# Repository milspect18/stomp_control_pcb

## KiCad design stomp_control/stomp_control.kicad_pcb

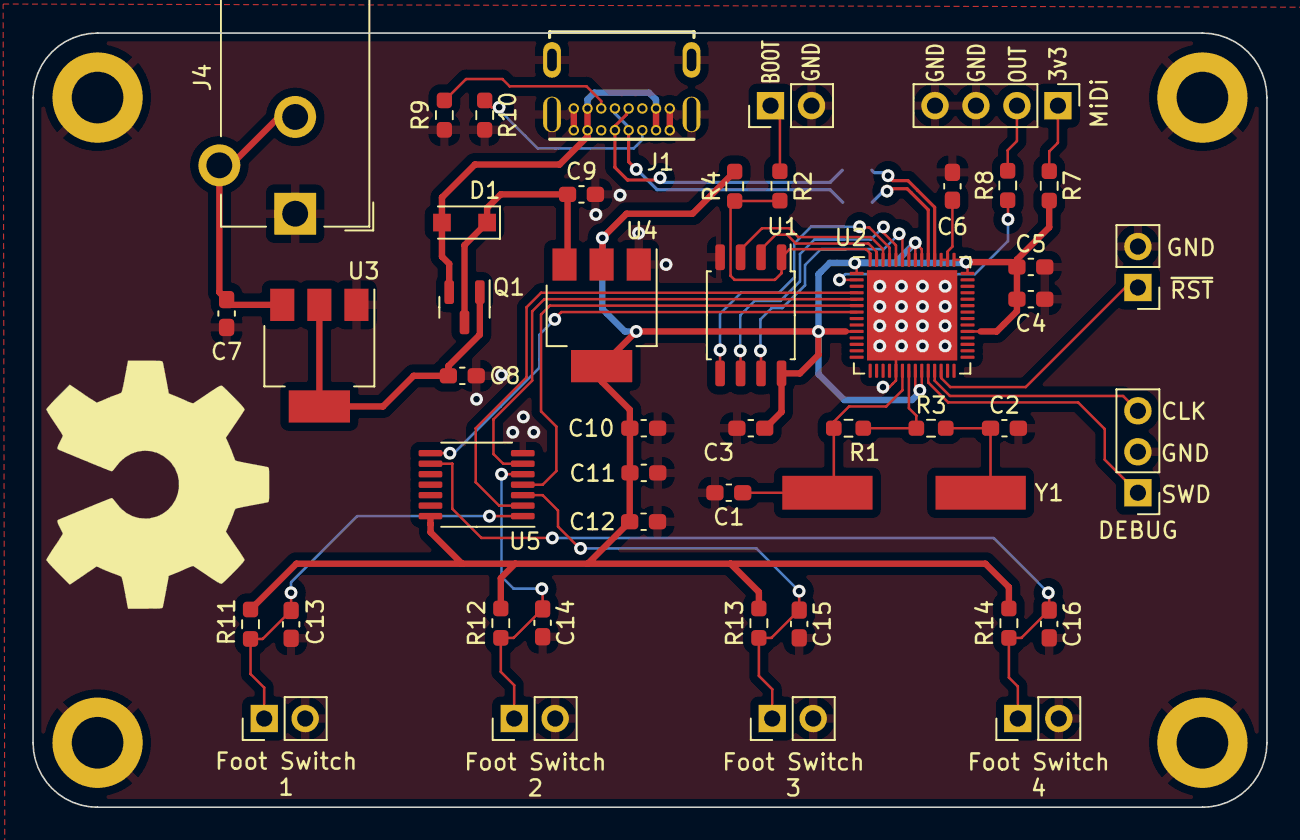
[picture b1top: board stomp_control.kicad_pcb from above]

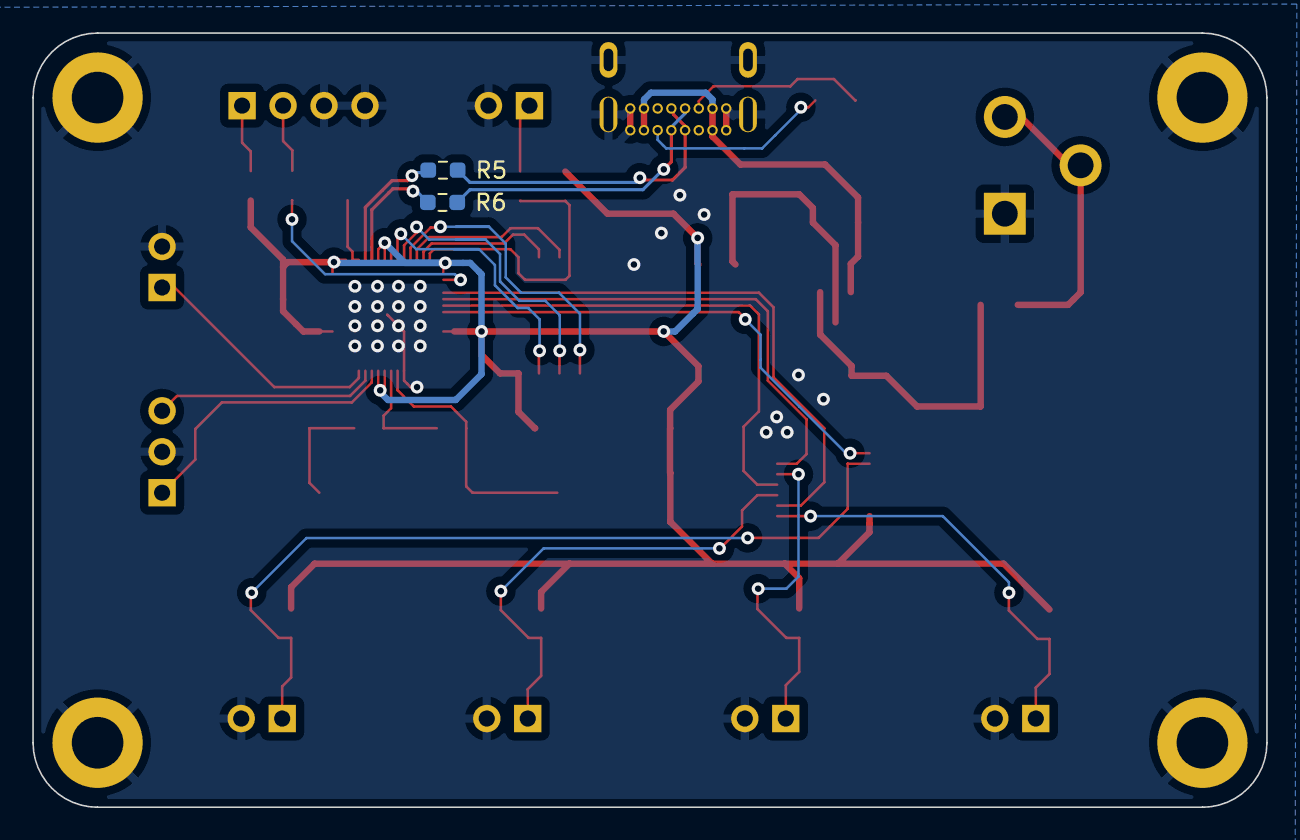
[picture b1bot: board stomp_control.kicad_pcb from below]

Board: 2 copper layers, 76.5 x 48.0 mm, 52 parts (2 on the bottom side), 37 nets.

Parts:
C1, C2: 15p; C_0603_1608Metric_Pad1.08x0.95mm_HandSolder
C3, C4, C13, C14, C15, C16: 100n; C_0603_1608Metric_Pad1.08x0.95mm_HandSolder
C5, C6: 2u2; C_0603_1608Metric_Pad1.08x0.95mm_HandSolder
C7, C8, C9, C10: 10uF; C_0603_1608Metric_Pad1.08x0.95mm_HandSolder
C11, C12: 10nF; C_0603_1608Metric_Pad1.08x0.95mm_HandSolder
D1: MBR1020VL; D_SOD-123F
DEBUG: SWD; PinHeader_1x03_P2.54mm_Vertical
H1, H2, H3, H4: MountingHole_Pad; MountingHole_3.2mm_M3_DIN965_Pad
J1: USB_C_Receptacle_USB2.0; GCT_USB4085-GF-A_REVA
J2: PROG_MODE; PinHeader_1x02_P2.54mm_Vertical
J3: RESET; PinHeader_1x02_P2.54mm_Vertical
J4: 9V center: Neg; BarrelJack_CUI_PJ-102AH_Horizontal
J5: Conn_01x04_Female; PinHeader_1x04_P2.54mm_Vertical
J6: FS_1; PinHeader_1x02_P2.54mm_Vertical
J7: FS_2; PinHeader_1x02_P2.54mm_Vertical
J8: FS_3; PinHeader_1x02_P2.54mm_Vertical
J9: FS_4; PinHeader_1x02_P2.54mm_Vertical
Q1: DMG2305UX; SOT-23
R1, R4: DNF; R_0603_1608Metric_Pad0.98x0.95mm_HandSolder
R2, R3: 1k; R_0603_1608Metric_Pad0.98x0.95mm_HandSolder
R5, R6: 27.4R; R_0603_1608Metric_Pad0.98x0.95mm_HandSolder
R7: 33R; R_0603_1608Metric_Pad0.98x0.95mm_HandSolder
R8: 10R; R_0603_1608Metric_Pad0.98x0.95mm_HandSolder
R9, R10: 5.1k; R_0603_1608Metric_Pad0.98x0.95mm_HandSolder
R11, R12, R13, R14: 220k; R_0603_1608Metric_Pad0.98x0.95mm_HandSolder
U1: W25Q128JVS; SOIC-8_5.23x5.23mm_P1.27mm
U2: RP2040; QFN-56-1EP_7x7mm_P0.4mm_EP5.6x5.6mm
U3: LM1117MP-5.0_NOPB; SOT-223
U4: LMS8117AMP-3.3_NOPB; SOT-223
U5: 74HC14; TSSOP-14_4.4x5mm_P0.65mm
Y1: 12MHz; ABLS-12.000MHZ-20-B-3-H-T

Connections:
/FootSwitches/3v3: C3.1, C4.1, C5.1, C10.1, C11.1, C12.1, R4.2, R7.2, R11.1, R12.1, R13.1, R14.1, U1.8 (VCC), U2.1 (IOVDD), U2.10 (IOVDD), U2.22 (IOVDD), U2.23 (DVDD), U2.33 (IOVDD), U2.42 (IOVDD), U2.43 (ADC_AVDD), U2.48 (USB_VDD), U2.49 (IOVDD), U2.50 (DVDD), U4.2 (VO), U4.4 (VO), U5.14 (VCC)
/FootSwitches/foot_switch_four: U2.7 (GPIO5), U5.8
/FootSwitches/foot_switch_one: U2.4 (GPIO2), U5.2
/FootSwitches/foot_switch_three: U2.6 (GPIO4), U5.4
/FootSwitches/foot_switch_two: U2.5 (GPIO3), U5.6
/MiDi/midi_out: R8.1, U2.2 (GPIO0)
/PSU/VBUS: D1.2 (A), J1.A4 (VBUS), J1.A9 (VBUS), J1.B4 (VBUS), J1.B9 (VBUS), Q1.2 (G)
/RP2040/1v1: C6.1, U2.44 (VREG_VIN), U2.45 (VREG_VOUT)
/RP2040/QSPI_CLK: U1.6 (CLK), U2.52 (QSPI_SCLK)
/RP2040/QSPI_SD0: U1.5 (DI(IO0)), U2.53 (QSPI_SD0)
/RP2040/QSPI_SD1: U1.2 (DO(IO1)), U2.55 (QSPI_SD1)
/RP2040/QSPI_SD2: U1.3 (IO2), U2.54 (QSPI_SD2)
/RP2040/QSPI_SD3: U1.7 (IO3), U2.51 (QSPI_SD3)
/RP2040/RP_USB_+: R5.1, U2.46 (USB_DM)
/RP2040/RP_USB_-: R6.1, U2.47 (USB_DP)
/RP2040/~QSPI_CS: R2.2, R4.1, U1.1 (~CS), U2.56 (QSPI_CSN)
/USB_+: J1.A6 (D+), J1.B6 (D+), R6.2
/USB_-: J1.A7 (D-), J1.B7 (D-), R5.2
GND: C1.1, C2.2, C3.2, C4.2, C5.2, C6.2, C7.2, C8.2, C9.2, C10.2, C11.2, C12.2, C13.2, C14.2, C15.2, C16.2, DEBUG.2, H1.1, H2.1, H3.1, H4.1, J1.A1 (GND), J1.A12 (GND), J1.B1 (GND), J1.B12 (GND), J1.S1 (SHIELD), J2.2, J3.2, J4.1, J5.3, J5.4, J6.2, J7.2, J8.2, J9.2, R9.2, R10.2, U1.4 (GND), U2.19 (TESTEN), U2.57 (GND), U3.1 (GND), U4.1 (GND), U5.7 (GND)
unnamed: C1.2, R1.1, U2.20 (XIN), Y1.1
unnamed: C2.1, R3.2, Y1.2
unnamed: C7.1, J4.2, J4.3, U3.3 (VI)
unnamed: C8.1, Q1.1 (D), U3.2 (VO), U3.4 (VO)
unnamed: C9.1, D1.1 (K), Q1.3 (S), U4.3 (VI)
unnamed: C13.1, J6.1, R11.2, U5.1
unnamed: C14.1, J7.1, R12.2, U5.5
unnamed: C15.1, J8.1, R13.2, U5.3
unnamed: C16.1, J9.1, R14.2, U5.9
unnamed: DEBUG.1, U2.24 (SWCLK)
unnamed: DEBUG.3, U2.25 (SWD)
unnamed: J2.1, R2.1
unnamed: J3.1, U2.26 (RUN)
unnamed: J5.1, R7.1
unnamed: J5.2, R8.2
unnamed: J1.A5 (CC1), R10.1
unnamed: J1.B5 (CC2), R9.1
unnamed: R1.2, R3.1, U2.21 (XOUT)

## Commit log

2021-12-21 setup initial kicad project. bring in rp2040 symbol
2021-12-22 initial schematic design
2021-12-22 ignore backups
2021-12-22 remove backups from scm
2021-12-22 initial board layout
2021-12-22 ignore gerber folder
2021-12-22 add silkscreen annotations
